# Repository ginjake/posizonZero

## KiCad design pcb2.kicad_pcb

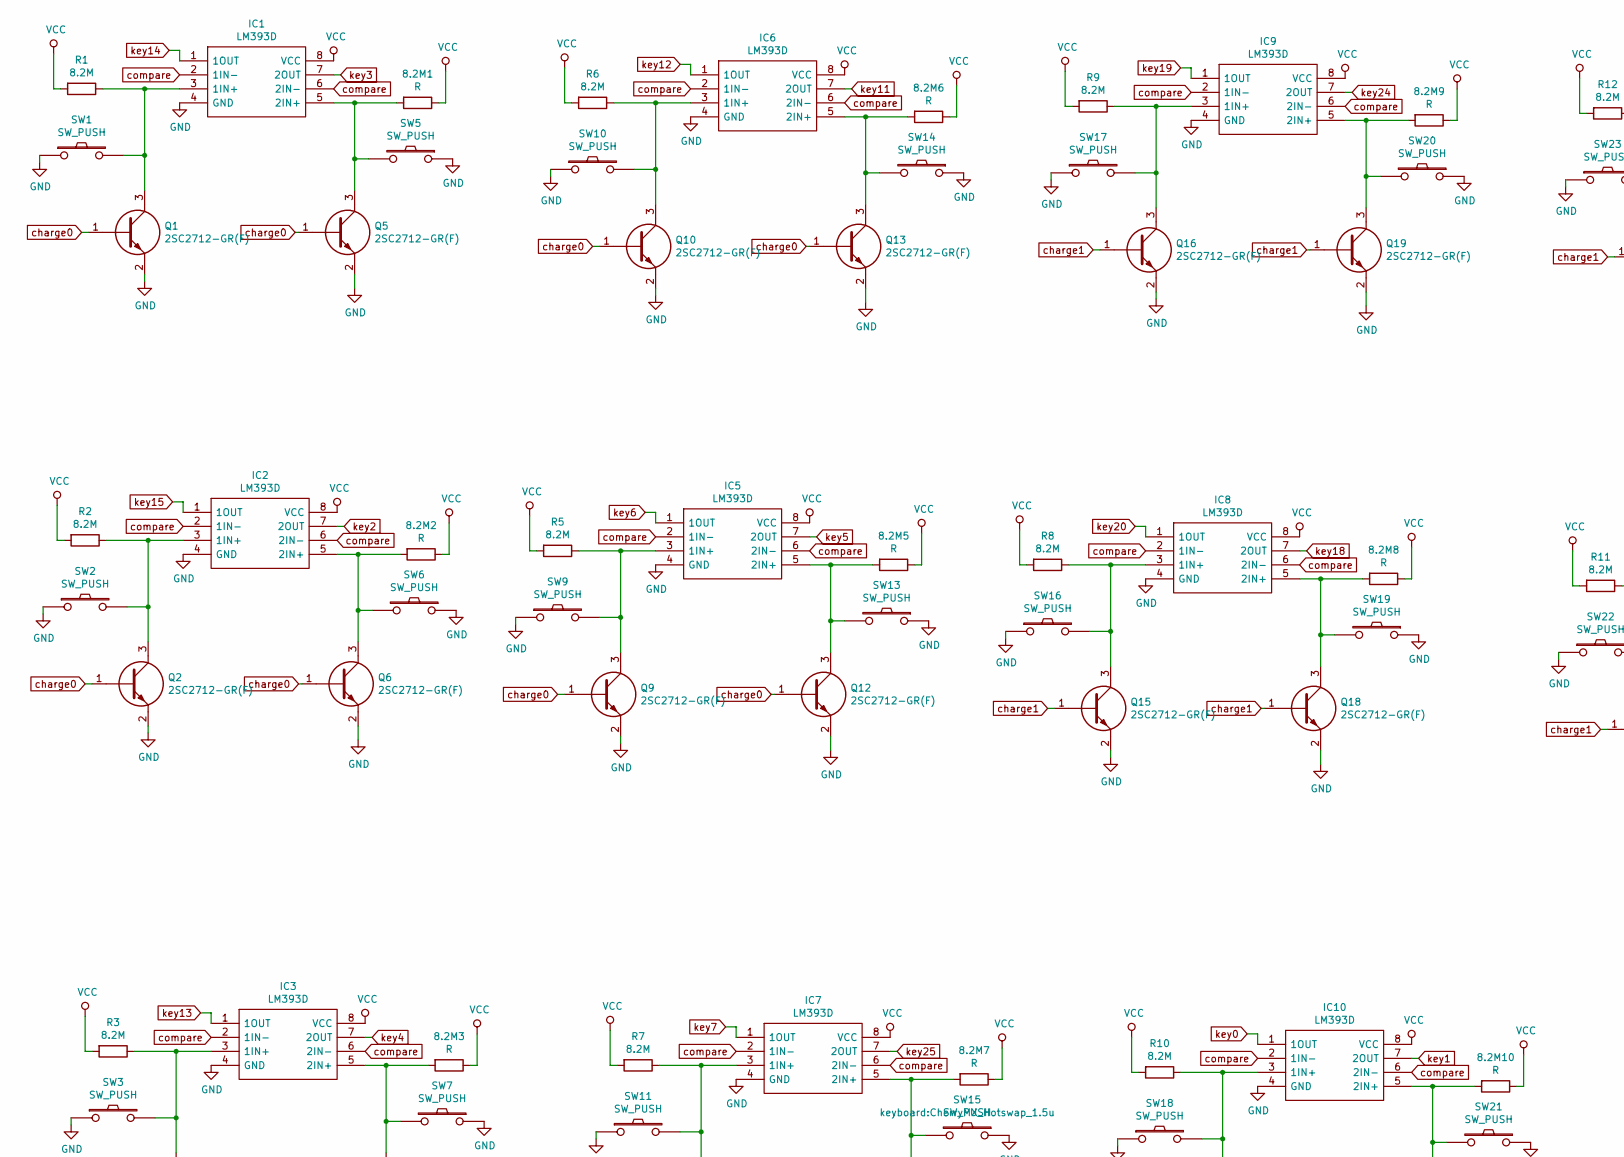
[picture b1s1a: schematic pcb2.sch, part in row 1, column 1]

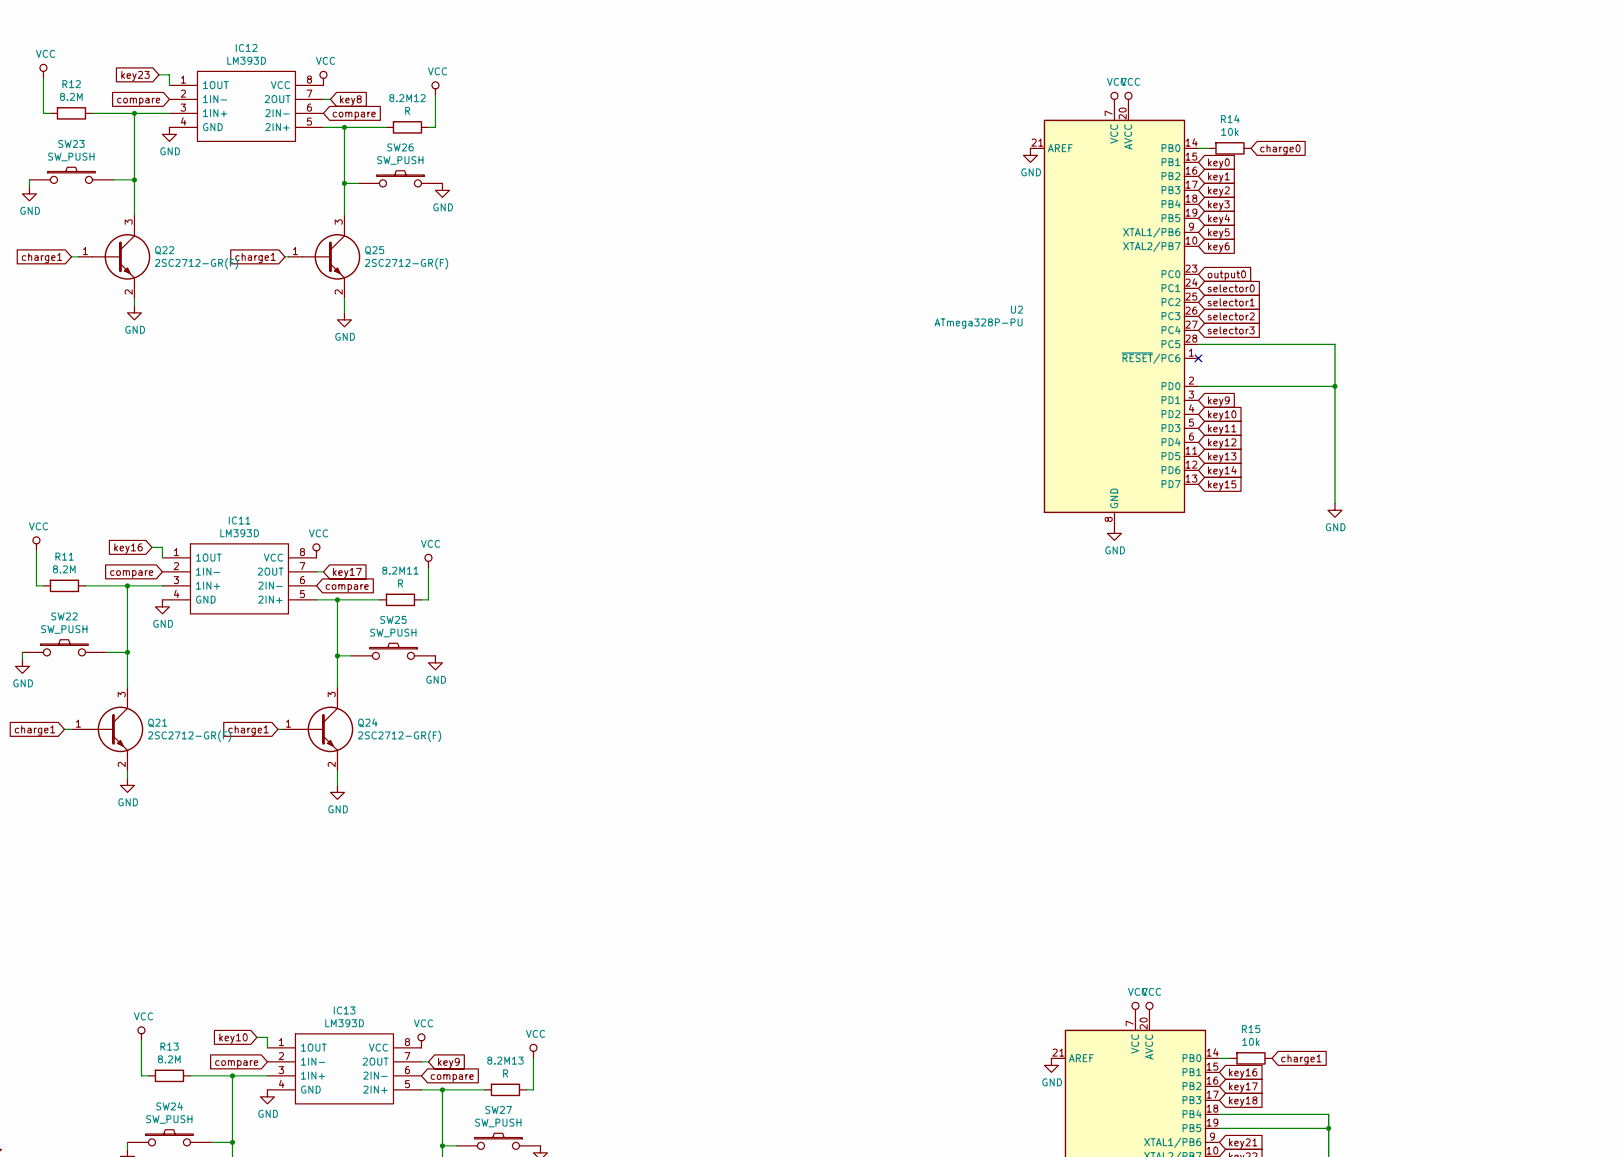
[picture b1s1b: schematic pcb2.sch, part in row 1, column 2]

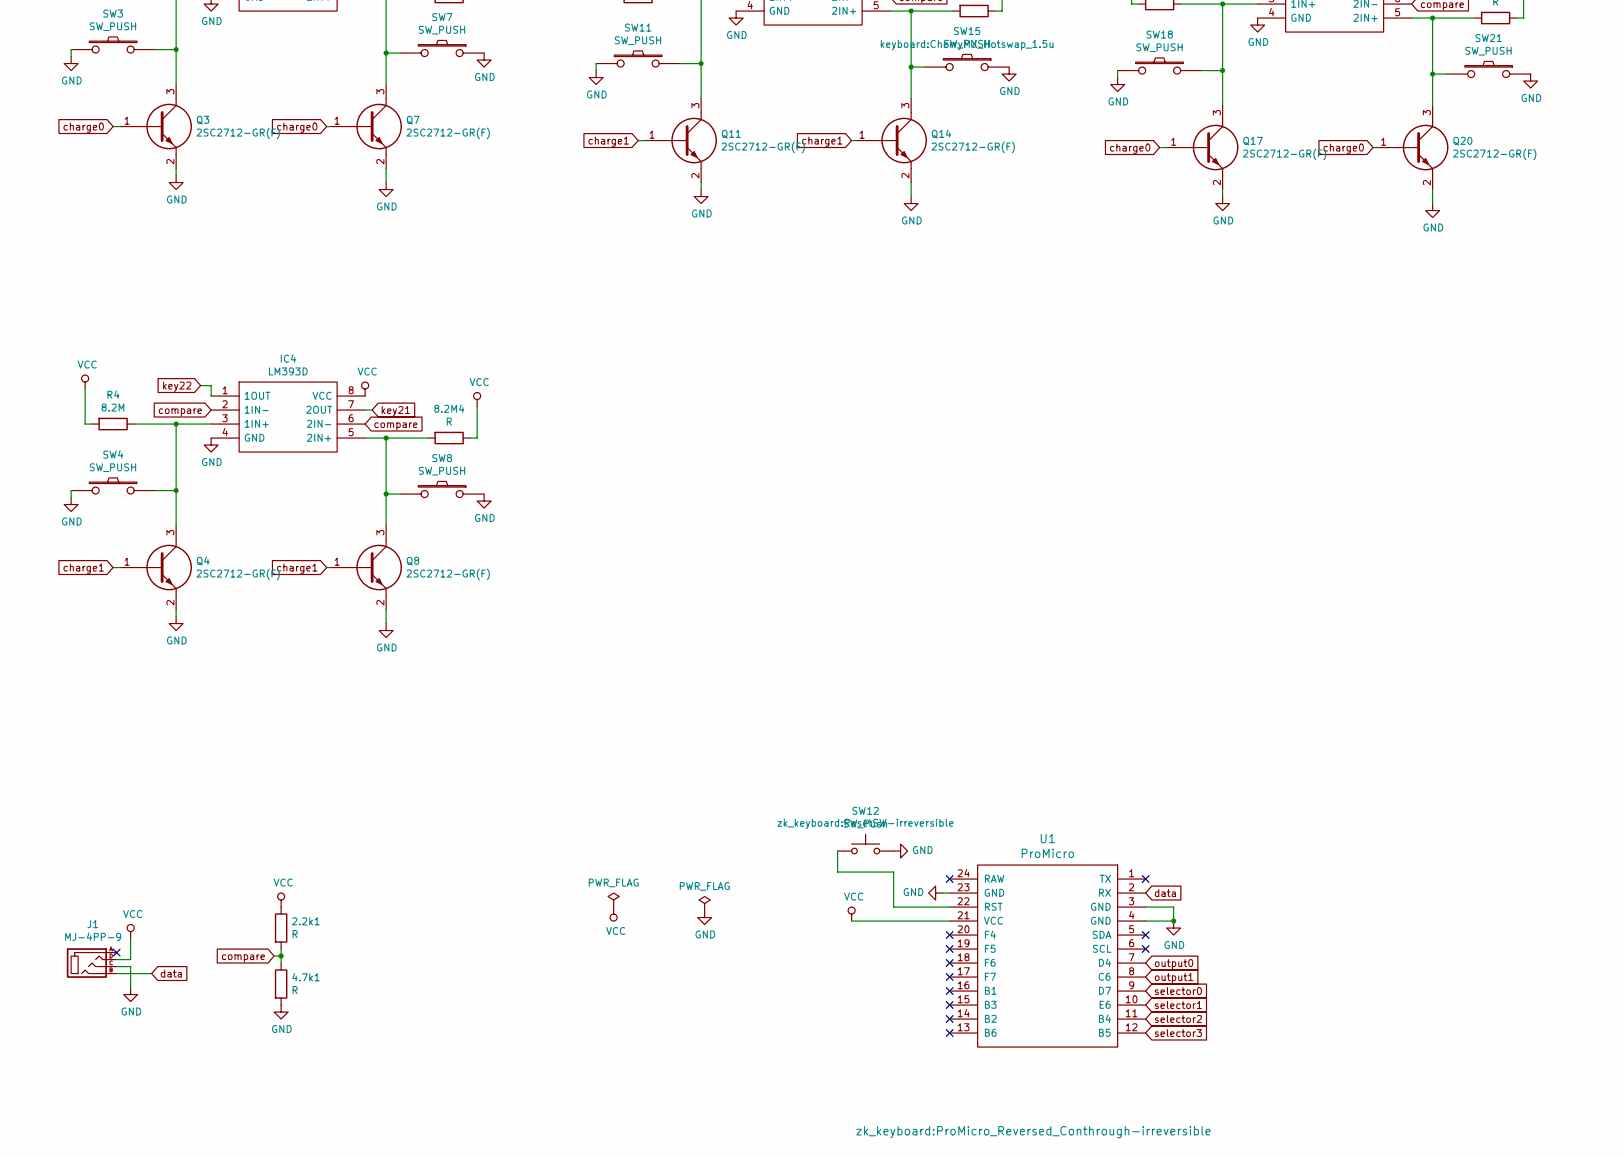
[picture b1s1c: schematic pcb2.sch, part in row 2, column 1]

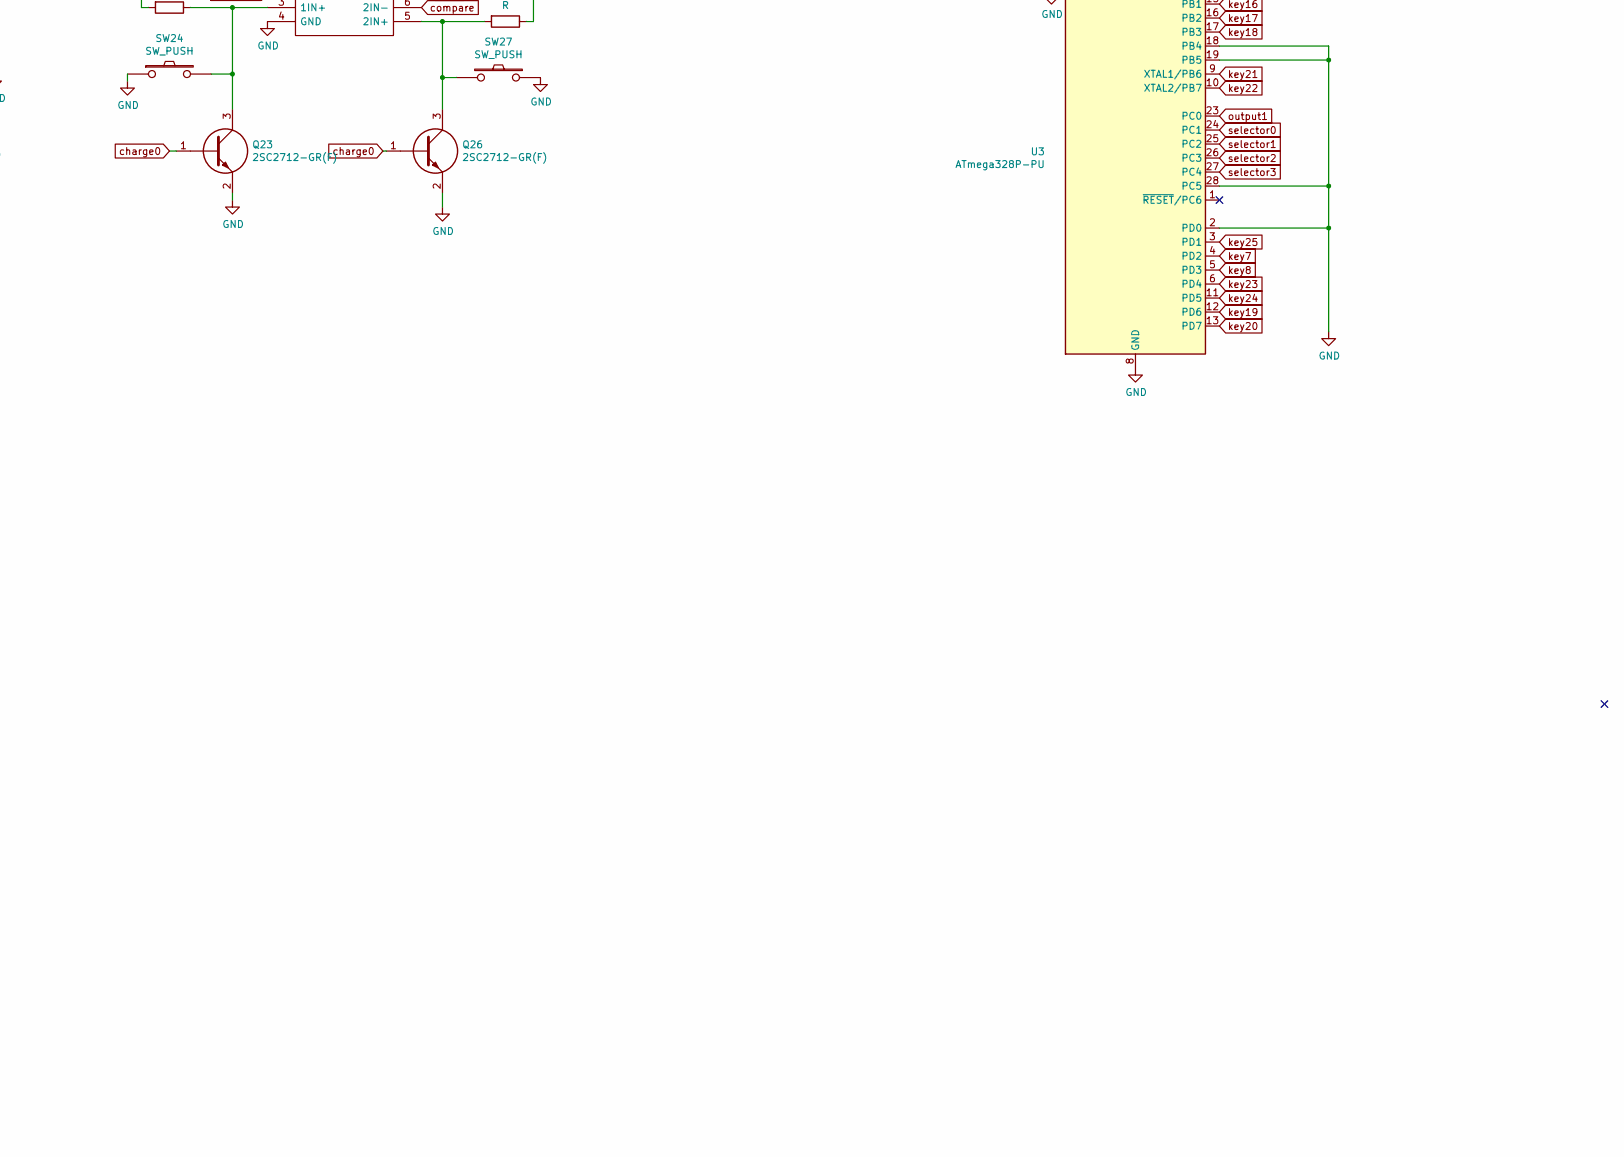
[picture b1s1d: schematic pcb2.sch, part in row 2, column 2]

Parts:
2.2k1, 4.7k1: R; R_Axial_DIN0204_L3.6mm_D1.6mm_P5.08mm_Vertical
8.2M1, 8.2M2, 8.2M3, 8.2M4, 8.2M5, 8.2M6, 8.2M7, 8.2M8, 8.2M9, 8.2M10, 8.2M11, 8.2M12, 8.2M13: R; R_Axial_DIN0207_L6.3mm_D2.5mm_P7.62mm_Horizontal
IC1, IC2, IC3, IC4, IC5, IC6, IC7, IC8, IC9, IC10, IC11, IC12, IC13: LM393D; SOIC127P600X175-8N; Manufacturer_Part_Number LM393D; Mouser Part Number 595-LM393D
J1: MJ-4PP-9; MJ-4PP-9_1side
Q1, Q2, Q3, Q4, Q5, Q6, Q7, Q8, Q9, Q10, Q11, Q12, Q13, Q14, Q15, Q16, Q17, Q18, Q19, Q20, Q21, Q22, Q23, Q24, Q25, Q26: 2SC2712-GR(F); SC-59; Manufacturer_Part_Number 2SC2712-GR(F)
R1, R2, R3, R4, R5, R6, R7, R8, R9, R10, R11, R12, R13: 8.2M; R_Axial_DIN0207_L6.3mm_D2.5mm_P7.62mm_Horizontal
R14, R15: 10k; R_Axial_DIN0204_L3.6mm_D1.6mm_P5.08mm_Vertical
SW1, SW2, SW3, SW4, SW5, SW6, SW7, SW8, SW9, SW10, SW11, SW13, SW14, SW16, SW17, SW18, SW19, SW20, SW21, SW22, SW23, SW24, SW25, SW26, SW27: SW_PUSH; CherryMX-Hotswap-v2
SW12: SW_Push; ResetSW-irreversible
SW15: SW_PUSH; CherryMX_Hotswap_1.5u
U1: ProMicro; ProMicro_Reversed_Conthrough-irreversible
U2, U3: ATmega328P-PU; DIP-28_W7.62mm

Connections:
GND: 4.7k1.2, IC1.4 (GND), IC2.4 (GND), IC3.4 (GND), IC4.4 (GND), IC5.4 (GND), IC6.4 (GND), IC7.4 (GND), IC8.4 (GND), IC9.4 (GND), IC10.4 (GND), IC11.4 (GND), IC12.4 (GND), IC13.4 (GND), J1.C, Q1.2, Q2.2, Q3.2, Q4.2, Q5.2, Q6.2, Q7.2, Q8.2, Q9.2, Q10.2, Q11.2, Q12.2, Q13.2, Q14.2, Q15.2, Q16.2, Q17.2, Q18.2, Q19.2, Q20.2, Q21.2, Q22.2, Q23.2, Q24.2, Q25.2, Q26.2, SW1.1, SW2.1, SW3.1, SW4.1, SW5.1, SW6.1, SW7.1, SW8.1, SW9.1, SW10.1, SW11.1, SW12.2, SW13.1, SW14.1, SW15.1, SW16.1, SW17.1, SW18.1, SW19.1, SW20.1, SW21.1, SW22.1, SW23.1, SW24.1, SW25.1, SW26.1, SW27.1, U1.3 (GND), U1.4 (GND), U1.23 (GND), U2.2 (PD0), U2.8 (GND), U2.21 (AREF), U2.22 (GND), U2.28 (PC5), U3.2 (PD0), U3.8 (GND), U3.18 (PB4), U3.19 (PB5), U3.21 (AREF), U3.22 (GND), U3.28 (PC5)
unnamed: 8.2M1.2, IC1.5 (2IN+), Q5.3, SW5.2
unnamed: 8.2M2.2, IC2.5 (2IN+), Q6.3, SW6.2
unnamed: 8.2M3.2, IC3.5 (2IN+), Q7.3, SW7.2
unnamed: 8.2M4.2, IC4.5 (2IN+), Q8.3, SW8.2
unnamed: 8.2M5.2, IC5.5 (2IN+), Q12.3, SW13.2
unnamed: 8.2M6.2, IC6.5 (2IN+), Q13.3, SW14.2
unnamed: 8.2M7.2, IC7.5 (2IN+), Q14.3, SW15.2
unnamed: 8.2M8.2, IC8.5 (2IN+), Q18.3, SW19.2
unnamed: 8.2M9.2, IC9.5 (2IN+), Q19.3, SW20.2
unnamed: 8.2M10.2, IC10.5 (2IN+), Q20.3, SW21.2
unnamed: 8.2M11.2, IC11.5 (2IN+), Q24.3, SW25.2
unnamed: 8.2M12.2, IC12.5 (2IN+), Q25.3, SW26.2
unnamed: 8.2M13.2, IC13.5 (2IN+), Q26.3, SW27.2
unnamed: IC1.3 (1IN+), Q1.3, R1.1, SW1.2
unnamed: IC2.3 (1IN+), Q2.3, R2.1, SW2.2
unnamed: IC3.3 (1IN+), Q3.3, R3.1, SW3.2
unnamed: IC4.3 (1IN+), Q4.3, R4.1, SW4.2
unnamed: IC5.3 (1IN+), Q9.3, R5.1, SW9.2
unnamed: IC6.3 (1IN+), Q10.3, R6.1, SW10.2
unnamed: IC7.3 (1IN+), Q11.3, R7.1, SW11.2
unnamed: IC8.3 (1IN+), Q15.3, R8.1, SW16.2
unnamed: IC9.3 (1IN+), Q16.3, R9.1, SW17.2
unnamed: IC10.3 (1IN+), Q17.3, R10.1, SW18.2
unnamed: IC11.3 (1IN+), Q21.3, R11.1, SW22.2
unnamed: IC12.3 (1IN+), Q22.3, R12.1, SW23.2
unnamed: IC13.3 (1IN+), Q23.3, R13.1, SW24.2
unnamed: R14.2, U2.14 (PB0)
unnamed: R15.2, U3.14 (PB0)
unnamed: SW12.1, U1.22 (RST)
VCC: 2.2k1.1, 8.2M1.1, 8.2M2.1, 8.2M3.1, 8.2M4.1, 8.2M5.1, 8.2M6.1, 8.2M7.1, 8.2M8.1, 8.2M9.1, 8.2M10.1, 8.2M11.1, 8.2M12.1, 8.2M13.1, IC1.8 (VCC), IC2.8 (VCC), IC3.8 (VCC), IC4.8 (VCC), IC5.8 (VCC), IC6.8 (VCC), IC7.8 (VCC), IC8.8 (VCC), IC9.8 (VCC), IC10.8 (VCC), IC11.8 (VCC), IC12.8 (VCC), IC13.8 (VCC), J1.D, R1.2, R2.2, R3.2, R4.2, R5.2, R6.2, R7.2, R8.2, R9.2, R10.2, R11.2, R12.2, R13.2, U1.21 (VCC), U2.7 (VCC), U2.20 (AVCC), U3.7 (VCC), U3.20 (AVCC)
charge0: Q1.1, Q2.1, Q3.1, Q5.1, Q6.1, Q7.1, Q9.1, Q10.1, Q12.1, Q13.1, Q17.1, Q20.1, Q23.1, Q26.1, R14.1
charge1: Q4.1, Q8.1, Q11.1, Q14.1, Q15.1, Q16.1, Q18.1, Q19.1, Q21.1, Q22.1, Q24.1, Q25.1, R15.1
compare: 2.2k1.2, 4.7k1.1, IC1.2 (1IN-), IC1.6 (2IN-), IC2.2 (1IN-), IC2.6 (2IN-), IC3.2 (1IN-), IC3.6 (2IN-), IC4.2 (1IN-), IC4.6 (2IN-), IC5.2 (1IN-), IC5.6 (2IN-), IC6.2 (1IN-), IC6.6 (2IN-), IC7.2 (1IN-), IC7.6 (2IN-), IC8.2 (1IN-), IC8.6 (2IN-), IC9.2 (1IN-), IC9.6 (2IN-), IC10.2 (1IN-), IC10.6 (2IN-), IC11.2 (1IN-), IC11.6 (2IN-), IC12.2 (1IN-), IC12.6 (2IN-), IC13.2 (1IN-), IC13.6 (2IN-)
data: J1.B, U1.2 (RX)
key0: IC10.1 (1OUT), U2.15 (PB1)
key1: IC10.7 (2OUT), U2.16 (PB2)
key2: IC2.7 (2OUT), U2.17 (PB3)
key3: IC1.7 (2OUT), U2.18 (PB4)
key4: IC3.7 (2OUT), U2.19 (PB5)
key5: IC5.7 (2OUT), U2.9 (XTAL1/PB6)
key6: IC5.1 (1OUT), U2.10 (XTAL2/PB7)
key7: IC7.1 (1OUT), U3.4 (PD2)
key8: IC12.7 (2OUT), U3.5 (PD3)
key9: IC13.7 (2OUT), U2.3 (PD1)
key10: IC13.1 (1OUT), U2.4 (PD2)
key11: IC6.7 (2OUT), U2.5 (PD3)
key12: IC6.1 (1OUT), U2.6 (PD4)
key13: IC3.1 (1OUT), U2.11 (PD5)
key14: IC1.1 (1OUT), U2.12 (PD6)
key15: IC2.1 (1OUT), U2.13 (PD7)
key16: IC11.1 (1OUT), U3.15 (PB1)
key17: IC11.7 (2OUT), U3.16 (PB2)
key18: IC8.7 (2OUT), U3.17 (PB3)
key19: IC9.1 (1OUT), U3.12 (PD6)
key20: IC8.1 (1OUT), U3.13 (PD7)
key21: IC4.7 (2OUT), U3.9 (XTAL1/PB6)
key22: IC4.1 (1OUT), U3.10 (XTAL2/PB7)
key23: IC12.1 (1OUT), U3.6 (PD4)
key24: IC9.7 (2OUT), U3.11 (PD5)
key25: IC7.7 (2OUT), U3.3 (PD1)
output0: U1.7 (D4), U2.23 (PC0)
output1: U1.8 (C6), U3.23 (PC0)
selector0: U1.9 (D7), U2.24 (PC1), U3.24 (PC1)
selector1: U1.10 (E6), U2.25 (PC2), U3.25 (PC2)
selector2: U1.11 (B4), U2.26 (PC3), U3.26 (PC3)
selector3: U1.12 (B5), U2.27 (PC4), U3.27 (PC4)

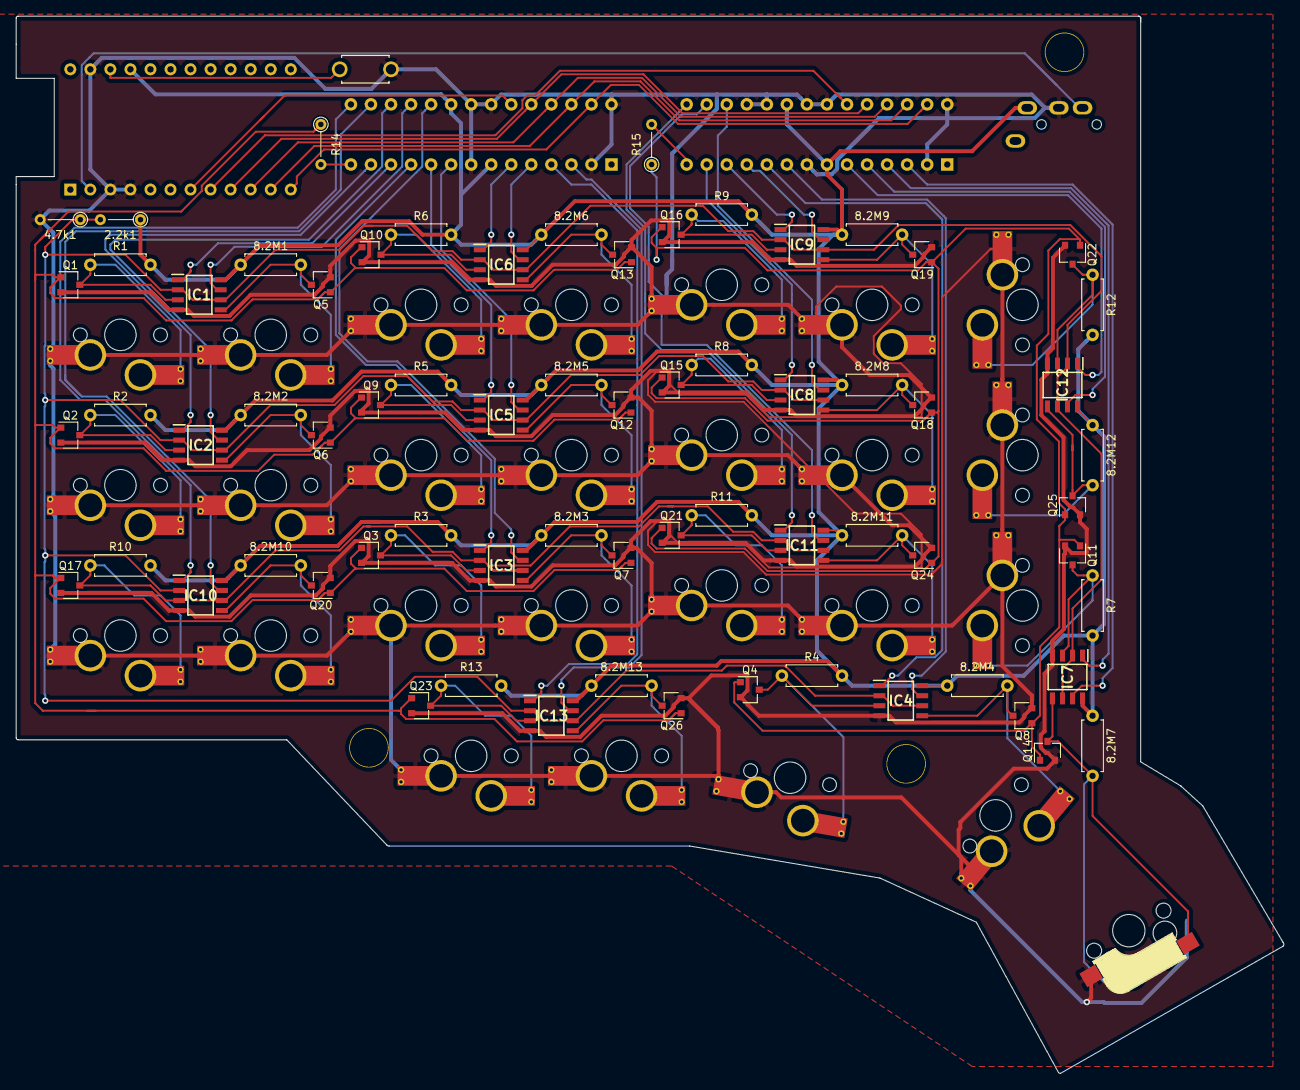
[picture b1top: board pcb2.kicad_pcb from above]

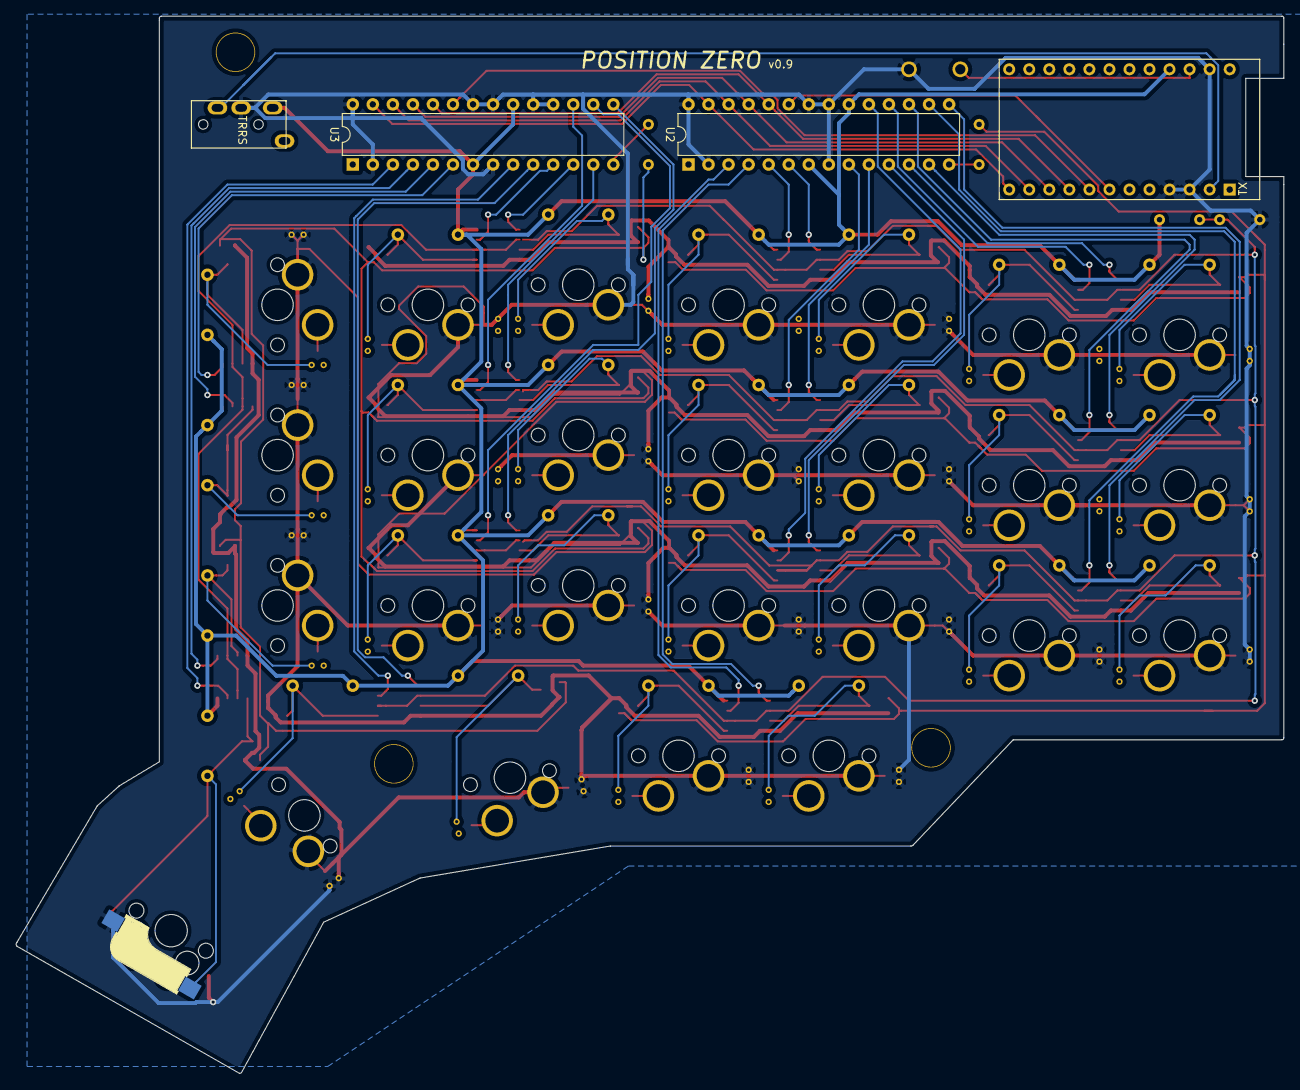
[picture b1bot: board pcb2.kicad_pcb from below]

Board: 2 copper layers, 160.6 x 134.0 mm, 103 parts (30 on the bottom side), 67 nets.

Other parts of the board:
Ref**: Val**; M2_SPACER_HOLE
Ref**#2, Ref**#3: Val**; M2_SPACER_HOLE

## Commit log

2019-11-13 きらめき
